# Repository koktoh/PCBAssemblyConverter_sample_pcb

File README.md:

# PCBAssemblyConverter_sample_pcb

Sample KiCad project for [PCBAssemblyConverter](https://koktoh.github.io/PCBAssemblyConverter/)

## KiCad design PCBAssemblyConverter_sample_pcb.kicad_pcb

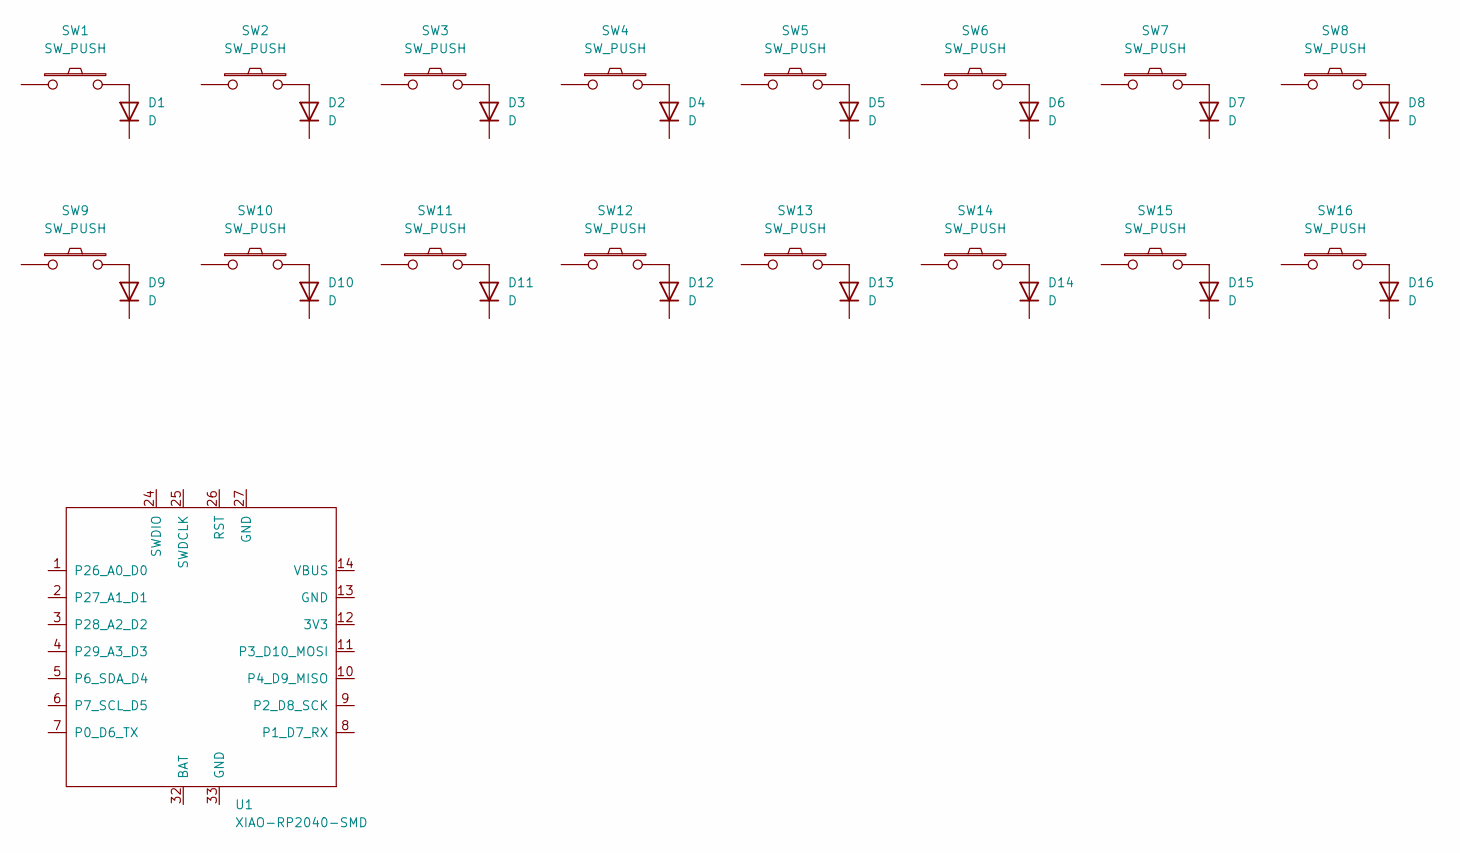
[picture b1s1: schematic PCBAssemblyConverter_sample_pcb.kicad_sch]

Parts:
D1, D2, D3, D4, D5, D6, D7, D8, D9, D10, D11, D12, D13, D14, D15, D16: D; D_SOD-123
SW1, SW2, SW3, SW4, SW5, SW6, SW7, SW8: SW_PUSH; CherryMX_Hotswap_via_1U
SW9, SW10, SW11, SW12, SW13, SW14, SW15, SW16: SW_PUSH; Kailh_Choc_V1_Hotswap_via
U1: XIAO-RP2040-SMD

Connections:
unnamed: D1.2 (A_2), SW1.2 (2_2)
unnamed: D2.2 (A_2), SW2.2 (2_2)
unnamed: D3.2 (A_2), SW3.2 (2_2)
unnamed: D4.2 (A_2), SW4.2 (2_2)
unnamed: D5.2 (A_2), SW5.2 (2_2)
unnamed: D6.2 (A_2), SW6.2 (2_2)
unnamed: D7.2 (A_2), SW7.2 (2_2)
unnamed: D8.2 (A_2), SW8.2 (2_2)
unnamed: D9.2 (A_2), SW9.2 (2_2)
unnamed: D10.2 (A_2), SW10.2 (2_2)
unnamed: D11.2 (A_2), SW11.2 (2_2)
unnamed: D12.2 (A_2), SW12.2 (2_2)
unnamed: D13.2 (A_2), SW13.2 (2_2)
unnamed: D14.2 (A_2), SW14.2 (2_2)
unnamed: D15.2 (A_2), SW15.2 (2_2)
unnamed: D16.2 (A_2), SW16.2 (2_2)

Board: 2 copper layers, 33 parts (17 on the bottom side), 16 nets, no tracks yet.

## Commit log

2026-06-08 add submodule
2026-06-08 create project
